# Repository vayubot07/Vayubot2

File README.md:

# Vayubot2
Autonomous AI-powered garbage collection drone by Rudra and Harsh

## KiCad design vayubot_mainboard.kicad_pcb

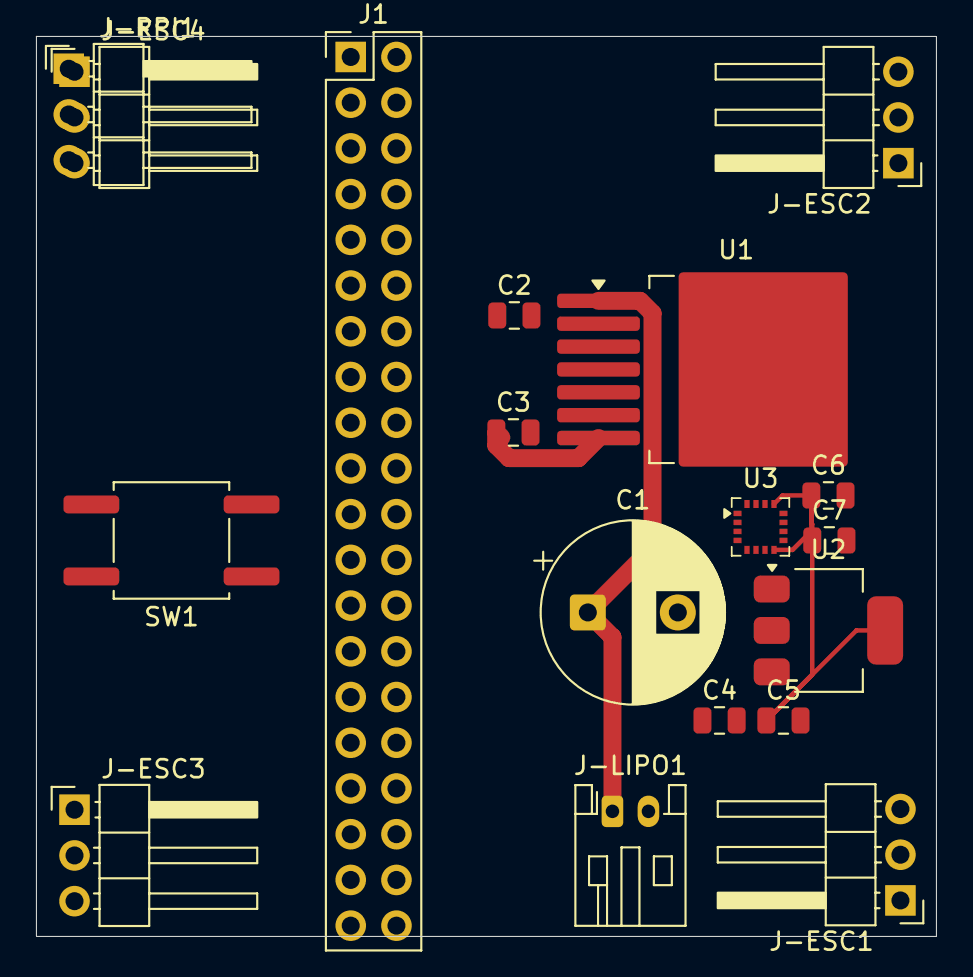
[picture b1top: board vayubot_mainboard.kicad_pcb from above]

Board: 2 copper layers, 50.0 x 50.0 mm, 18 parts (0 on the bottom side), 5 nets.

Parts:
C1: 1000uF; CP_Radial_D10.0mm_P5.00mm
C2: 10uF; C_0805_2012Metric
C3: 47uF; C_0805_2012Metric
C4, C5, C6, C7: 0.1uF; C_0805_2012Metric
J1: Conn_02x20_Odd_Even; PinHeader_2x20_P2.54mm_Vertical
J-ESC1, J-ESC2, J-ESC3, J-ESC4: Conn_01x03_Pin; PinHeader_1x03_P2.54mm_Horizontal
J-LIPO1: Conn_01x02_Pin; JST_PH_S2B-PH-K_1x02_P2.00mm_Horizontal
J-RPI1: Conn_01x40_Pin; PinHeader_1x03_P2.54mm_Horizontal
SW1: SW_Push; SW_Push_1P1T_NO_CK_KSC6xxG
U1: 171050601; TO-263-7_TabPin8
U2: AMS1117-3.3; SOT-223-3_TabPin2
U3: MPU-9250; LGA-16_3x3mm_P0.5mm

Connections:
GND: C1.2, J-ESC2.3, J-ESC4.3
unnamed: C2.2, C3.2, C4.1, C4.2, C5.2, C6.2, C7.2, J-ESC1.3, J-ESC3.3, J-LIPO1.2, J-RPI1.2, SW1.1, U1.4 (AGND), U1.8 (PGND), U2.1 (GND), U2.3 (VI)
unnamed: C3.1, U1.7 (VOUT)
V-BATT: C1.1, C2.1, J-ESC1.1, J-ESC2.1, J-ESC3.1, J-ESC4.1, J-LIPO1.1, U1.1 (VIN), U1.3 (EN)
VCC_3V3: C5.1, C6.1, C7.1, U2.2 (VO), U3.8 (VDDIO), U3.13 (VDD)
